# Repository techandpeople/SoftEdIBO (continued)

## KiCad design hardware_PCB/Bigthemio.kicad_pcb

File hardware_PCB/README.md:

# Hardware (PCB) files

KiCad design files for the SoftEdIBO node boards:

- **Top-level KiCad project** (the `.kicad_pro` / `.kicad_sch` / `.kicad_pcb`
  files in this directory) — the **multiplexed board** (`node_multiplexed`):
  ESP32-WROOM-32, 74HC4067 sensor mux, PCA9685-driven valves (ULN2803 drivers),
  up to 6 pumps, XGZP6847A pressure sensors.
- **Nested KiCad project** (the subdirectory with its own `.kicad_pro`) — the
  **direct board** (`node_direct`): ESP32-WROOM-32, 3 chambers on direct ADC
  sensors, ULN2803-driven valves, 2 onboard pumps.
- `Data_sheets/` — component datasheets (pump/valve drivers, XGZP6847A pressure
  sensor).
- `libraries/` — shared KiCad symbol/footprint libraries;
  `logic_I2C.kicad_sch` — shared I2C logic sheet.

> The project files carry legacy names on disk; in code and docs the boards are
> always referred to by their functional names — the **direct board**
> (`node_direct`, firmware env `direct`) and the **multiplexed board**
> (`node_multiplexed`, firmware env `multiplexed`). See
> [firmware/node_actuator/](../firmware/node_actuator/).

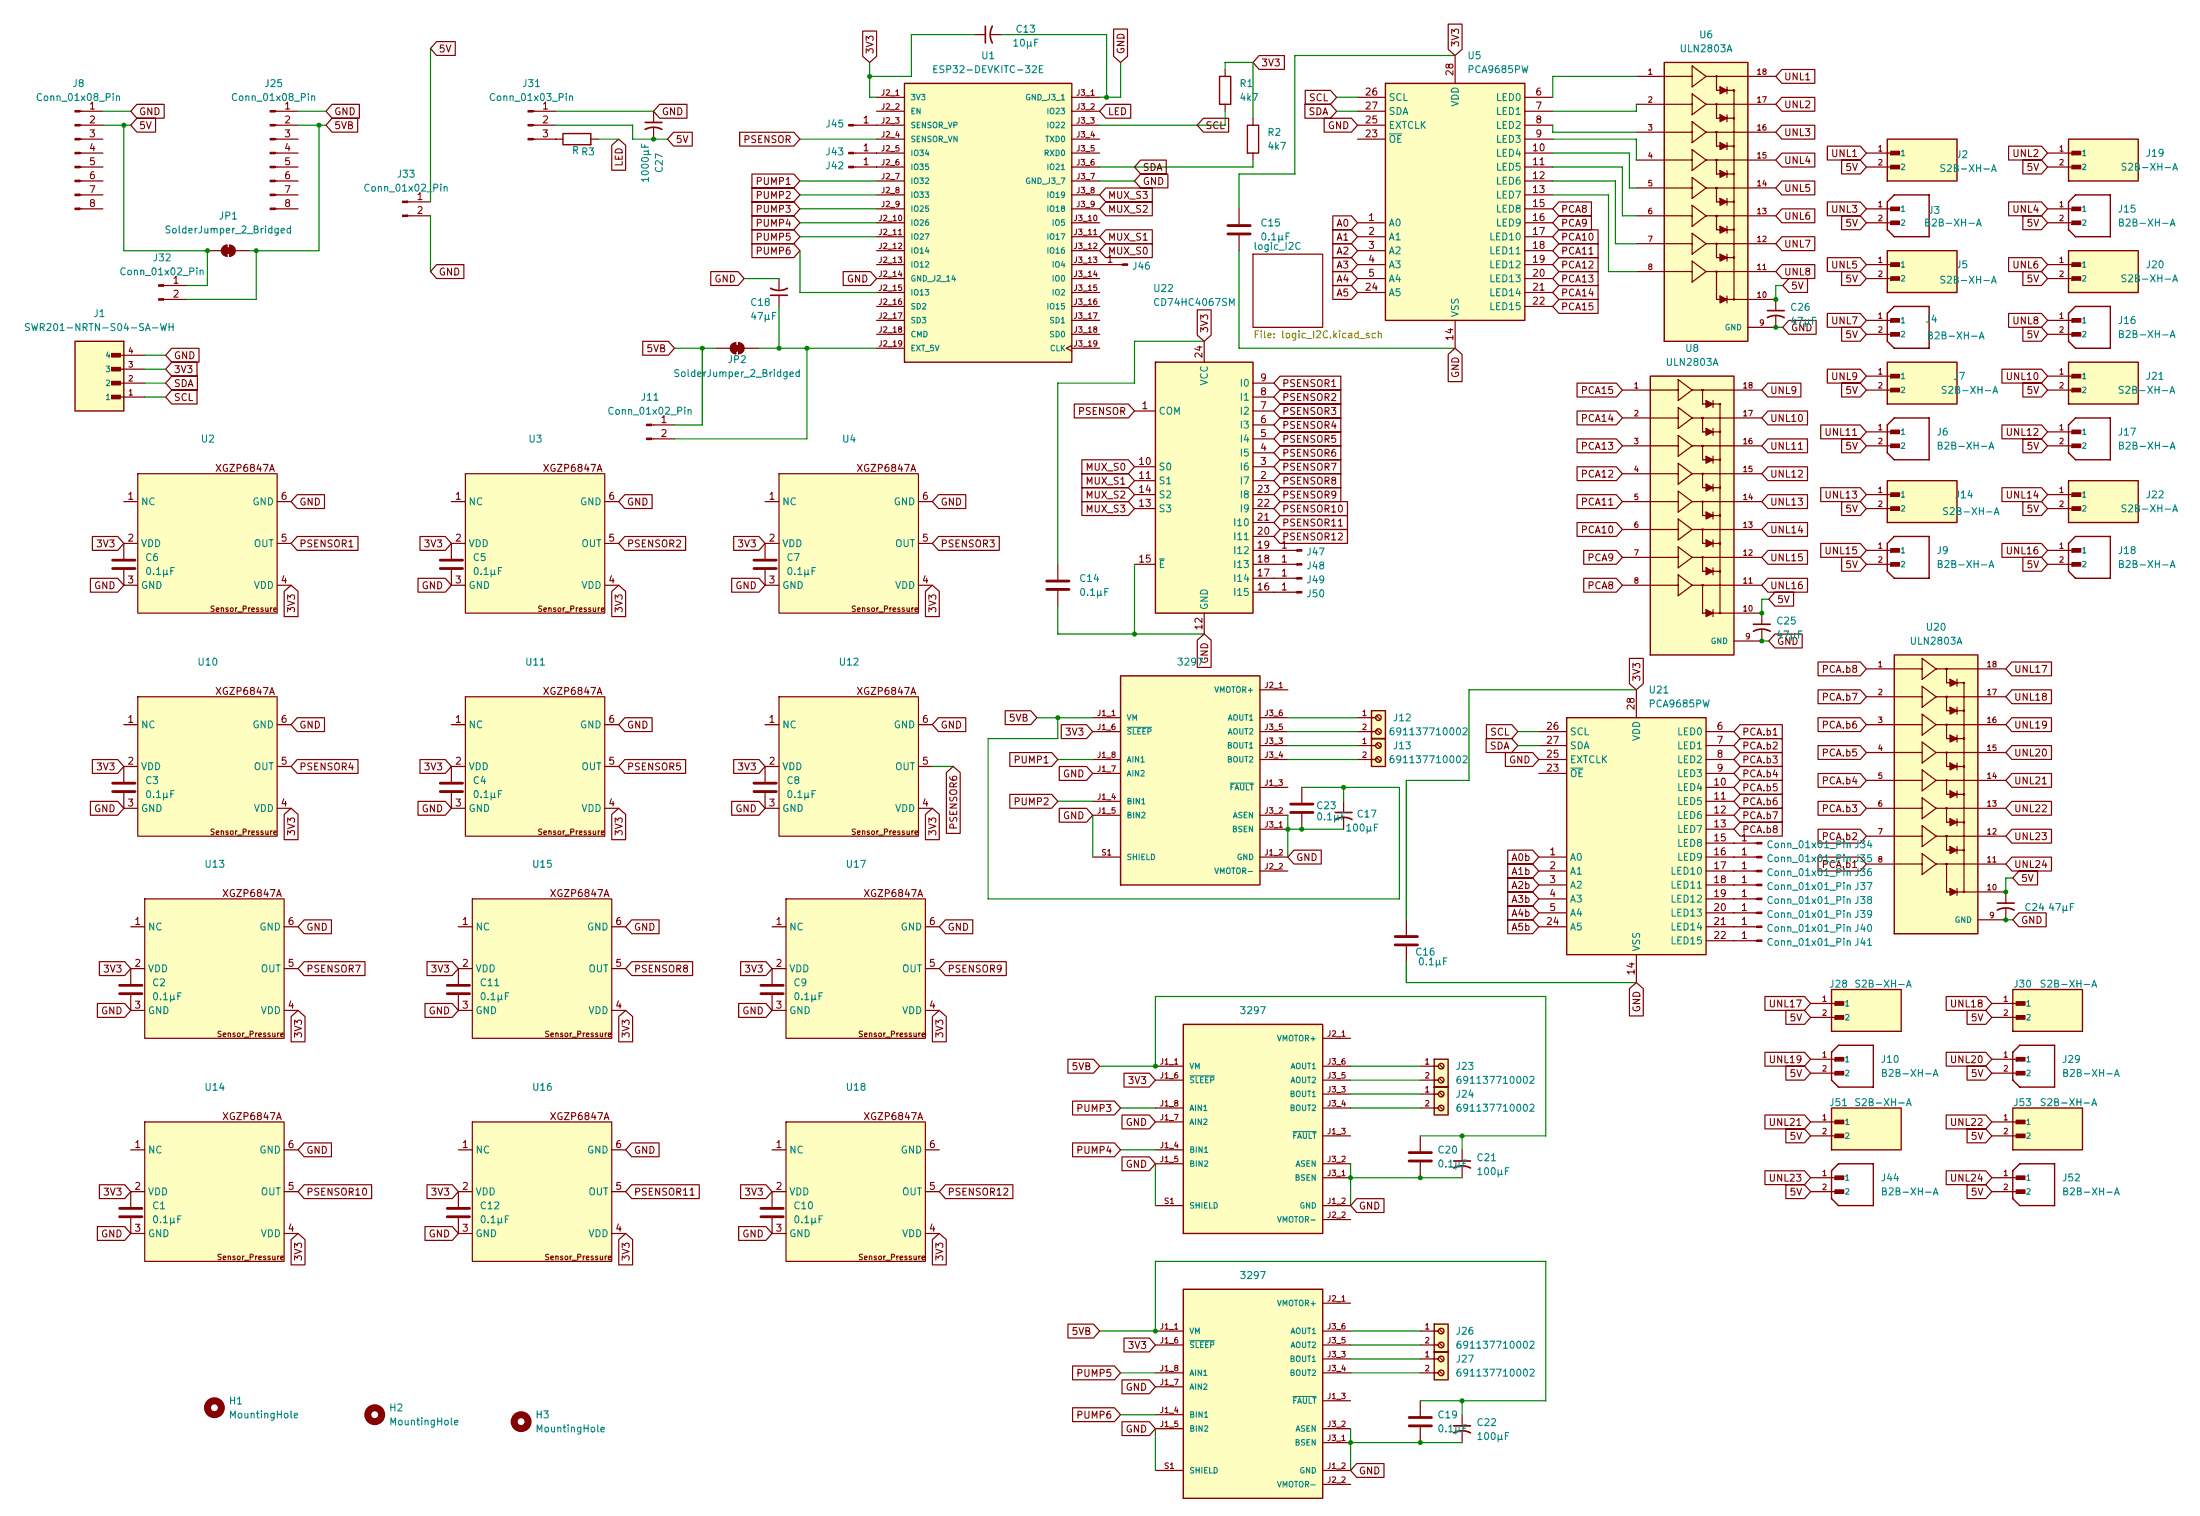
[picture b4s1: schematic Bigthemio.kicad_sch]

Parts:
C1, C2, C3, C4, C5, C6, C7, C8, C9, C10, C11, C12, C14, C15, C16, C19, C20, C23: 0.1µF; C_Disc_D5.0mm_W2.5mm_P5.00mm
C13: 10µF; CP_Radial_D5.0mm_P2.00mm
C17, C21, C22: 100µF; CP_Radial_D5.0mm_P2.00mm
C18, C24, C25, C26: 47µF; CP_Radial_D5.0mm_P2.00mm
C27: 1000µF; CP_Radial_D5.0mm_P2.00mm
H1, H2, H3: MountingHole; MountingHole_4.3mm_M4
J1: SWR201-NRTN-S04-SA-WH; SULLINS_SWR201-NRTN-S04-SA-WH; PARTREV A
J2, J5, J7, J14, J19, J20, J21, J22, J28, J30, J51, J53: S2B-XH-A; JST_S2B-XH-A
J3, J4, J6, J9, J10, J15, J16, J17, J18, J29, J44, J52: B2B-XH-A; JST_B2B-XH-A; PARTREV N/A
J8, J25: Conn_01x08_Pin; PinHeader_1x08_P2.54mm_Vertical
J11, J32, J33: Conn_01x02_Pin; PinHeader_1x02_P2.54mm_Vertical
J12, J13, J23, J24, J26, J27: 691137710002
J31: Conn_01x03_Pin; PinHeader_1x03_P2.54mm_Vertical
J34, J35, J36, J37, J38, J39, J40, J41, J42, J43, J45, J46, J47, J48, J49, J50: Conn_01x01_Pin; PinHeader_1x01_P2.54mm_Vertical
JP1, JP2: SolderJumper_2_Bridged; SolderJumper-2_P1.3mm_Bridged2Bar_RoundedPad1.0x1.5mm
R1, R2: 4k7; R_Axial_DIN0207_L6.3mm_D2.5mm_P7.62mm_Horizontal
R3: R; R_Axial_DIN0207_L6.3mm_D2.5mm_P7.62mm_Horizontal
U1: ESP32-DEVKITC-32E; MODULE_ESP32-DEVKITC-32E; PARTREV 1.4
U2, U3, U4, U10, U11, U12, U13, U14, U15, U16, U17, U18: XGP6847A_TiagoDias
U5, U21: PCA9685PW; TSSOP-28_4.4x9.7mm_P0.65mm
U6, U8, U20: ULN2803A; UNL; PARTREV 4
U7, U9, U19: 3297; MODULE_3297; PARTREV 2020-11-20
U22: CD74HC4067SM; SSOP-24_5.3x8.2mm_P0.65mm

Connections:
3V3: C1.1, C2.1, C3.1, C4.1, C5.1, C6.1, C7.1, C8.1, C9.1, C10.1, C11.1, C12.1, C13.1, C14.1, C15.1, C16.1, J1.3, R1.1, R2.1, U1.J2_1 (3V3), U2.2 (VDD), U2.4 (VDD), U3.2 (VDD), U3.4 (VDD), U4.2 (VDD), U4.4 (VDD), U5.28 (VDD), U7.J1_6 (~SLEEP), U9.J1_6 (~SLEEP), U10.2 (VDD), U10.4 (VDD), U11.2 (VDD), U11.4 (VDD), U12.2 (VDD), U12.4 (VDD), U13.2 (VDD), U13.4 (VDD), U14.2 (VDD), U14.4 (VDD), U15.2 (VDD), U15.4 (VDD), U16.2 (VDD), U16.4 (VDD), U17.2 (VDD), U17.4 (VDD), U18.2 (VDD), U18.4 (VDD), U19.J1_6 (~SLEEP), U21.28 (VDD), U22.24 (VCC); also elsewhere on the board
5V: C24.1, C25.1, C26.1, C27.2, J2.2, J3.2, J4.2, J5.2, J6.2, J7.2, J8.2, J9.2, J10.2, J14.2, J15.2, J16.2, J17.2, J18.2, J19.2, J20.2, J21.2, J22.2, J28.2, J29.2, J30.2, J31.2, J32.1, J33.1, J44.2, J51.2, J52.2, J53.2, JP1.1 (A), U6.10, U8.10, U20.10
5VB: C17.1, C19.1, C20.1, C21.1, C22.1, C23.1, J11.1, J25.2, J32.2, JP1.2 (B), JP2.1 (A), U7.J1_1 (VM), U9.J1_1 (VM), U19.J1_1 (VM)
A0: U5.1 (A0); also elsewhere on the board
A0b: U21.1 (A0); also elsewhere on the board
A1: U5.2 (A1); also elsewhere on the board
A1b: U21.2 (A1); also elsewhere on the board
A2: U5.3 (A2); also elsewhere on the board
A2b: U21.3 (A2); also elsewhere on the board
A3: U5.4 (A3); also elsewhere on the board
A3b: U21.4 (A3); also elsewhere on the board
A4: U5.5 (A4); also elsewhere on the board
A4b: U21.5 (A4); also elsewhere on the board
A5: U5.24 (A5); also elsewhere on the board
A5b: U21.24 (A5); also elsewhere on the board
GND: C1.2, C2.2, C3.2, C4.2, C5.2, C6.2, C7.2, C8.2, C9.2, C10.2, C11.2, C12.2, C13.2, C14.2, C15.2, C16.2, C17.2, C18.2, C19.2, C20.2, C21.2, C22.2, C23.2, C24.2, C25.2, C26.2, C27.1, J1.4, J8.1, J25.1, J31.1, J33.2, U1.J2_14 (GND_J2_14), U1.J3_1 (GND_J3_1), U1.J3_7 (GND_J3_7), U2.3 (GND), U2.6 (GND), U3.3 (GND), U3.6 (GND), U4.3 (GND), U4.6 (GND), U5.14 (VSS), U5.25 (EXTCLK), U6.9 (GND), U7.J1_2 (GND), U7.J1_5 (BIN2), U7.J1_7 (AIN2), U7.J3_1 (BSEN), U7.J3_2 (ASEN), U7.S1 (SHIELD), U7.S2 (SHIELD), U8.9 (GND), U9.J1_2 (GND), U9.J1_5 (BIN2), U9.J1_7 (AIN2), U9.J3_1 (BSEN), U9.J3_2 (ASEN), U9.S1 (SHIELD), U9.S2 (SHIELD), U10.3 (GND), U10.6 (GND), U11.3 (GND), U11.6 (GND), U12.3 (GND), U12.6 (GND), U13.3 (GND), U13.6 (GND), U14.3 (GND), U14.6 (GND), U15.3 (GND), U15.6 (GND), U16.3 (GND), U16.6 (GND), U17.3 (GND), U17.6 (GND), U18.3 (GND), U19.J1_2 (GND), U19.J1_5 (BIN2), U19.J1_7 (AIN2), U19.J3_1 (BSEN), U19.J3_2 (ASEN), U19.S1 (SHIELD), U19.S2 (SHIELD), U20.9 (GND), U21.14 (VSS), U21.25 (EXTCLK), U22.12 (GND), U22.15 (~E); also elsewhere on the board
LED: R3.2, U1.J3_2 (IO23)
MUX_S0: U1.J3_12 (IO16), U22.10 (S0)
MUX_S1: U1.J3_11 (IO17), U22.11 (S1)
MUX_S2: U1.J3_9 (IO18), U22.14 (S2)
MUX_S3: U1.J3_8 (IO19), U22.13 (S3)
unnamed: C18.1, J11.2, JP2.2 (B), U1.J2_19 (EXT_5V)
unnamed: J31.3, R3.1
unnamed: J34.1, U21.15 (LED8)
unnamed: J35.1, U21.16 (LED9)
unnamed: J36.1, U21.17 (LED10)
unnamed: J37.1, U21.18 (LED11)
unnamed: J38.1, U21.19 (LED12)
unnamed: J39.1, U21.20 (LED13)
unnamed: J40.1, U21.21 (LED14)
unnamed: J41.1, U21.22 (LED15)
unnamed: J42.1, U1.J2_6 (IO35)
unnamed: J43.1, U1.J2_5 (IO34)
unnamed: J45.1, U1.J2_3 (SENSOR_VP)
unnamed: J46.1, U1.J3_13 (IO4)
unnamed: J47.1, U22.19 (I12)
unnamed: J48.1, U22.18 (I13)
unnamed: J49.1, U22.17 (I14)
unnamed: J50.1, U22.16 (I15)
unnamed: U5.6 (LED0), U6.1
unnamed: U5.7 (LED1), U6.2
unnamed: U5.8 (LED2), U6.3
unnamed: U5.9 (LED3), U6.4
unnamed: U5.10 (LED4), U6.5
unnamed: U5.11 (LED5), U6.6
unnamed: U5.12 (LED6), U6.7
unnamed: U5.13 (LED7), U6.8
unnamed: J12.1, U7.J3_6 (AOUT1)
unnamed: J12.2, U7.J3_5 (AOUT2)
unnamed: J13.1, U7.J3_3 (BOUT1)
unnamed: J13.2, U7.J3_4 (BOUT2)
unnamed: J23.1, U9.J3_6 (AOUT1)
unnamed: J23.2, U9.J3_5 (AOUT2)
unnamed: J24.1, U9.J3_3 (BOUT1)
unnamed: J24.2, U9.J3_4 (BOUT2)
unnamed: J26.1, U19.J3_6 (AOUT1)
unnamed: J26.2, U19.J3_5 (AOUT2)
unnamed: J27.1, U19.J3_3 (BOUT1)
unnamed: J27.2, U19.J3_4 (BOUT2)
PCA8: U5.15 (LED8), U8.8
PCA9: U5.16 (LED9), U8.7
PCA10: U5.17 (LED10), U8.6
PCA11: U5.18 (LED11), U8.5
PCA12: U5.19 (LED12), U8.4
PCA13: U5.20 (LED13), U8.3
PCA14: U5.21 (LED14), U8.2
PCA15: U5.22 (LED15), U8.1
PCA.b1: U20.8, U21.6 (LED0)
PCA.b2: U20.7, U21.7 (LED1)
PCA.b3: U20.6, U21.8 (LED2)
PCA.b4: U20.5, U21.9 (LED3)
PCA.b5: U20.4, U21.10 (LED4)
PCA.b6: U20.3, U21.11 (LED5)
PCA.b7: U20.2, U21.12 (LED6)
PCA.b8: U20.1, U21.13 (LED7)
PSENSOR: U1.J2_4 (SENSOR_VN), U22.1 (COM)
PSENSOR1: U2.5 (OUT), U22.9 (I0)
PSENSOR2: U3.5 (OUT), U22.8 (I1)
PSENSOR3: U4.5 (OUT), U22.7 (I2)
PSENSOR4: U10.5 (OUT), U22.6 (I3)
PSENSOR5: U11.5 (OUT), U22.5 (I4)
PSENSOR6: U12.5 (OUT), U22.4 (I5)
PSENSOR7: U13.5 (OUT), U22.3 (I6)
PSENSOR8: U15.5 (OUT), U22.2 (I7)
PSENSOR9: U17.5 (OUT), U22.23 (I8)
PSENSOR10: U14.5 (OUT), U22.22 (I9)
PSENSOR11: U16.5 (OUT), U22.21 (I10)
PSENSOR12: U18.5 (OUT), U22.20 (I11)
PUMP1: U1.J2_7 (IO32), U7.J1_8 (AIN1)
PUMP2: U1.J2_8 (IO33), U7.J1_4 (BIN1)
PUMP3: U1.J2_9 (IO25), U9.J1_8 (AIN1)
PUMP4: U1.J2_10 (IO26), U9.J1_4 (BIN1)
PUMP5: U1.J2_11 (IO27), U19.J1_8 (AIN1)
PUMP6: U1.J2_15 (IO13), U19.J1_4 (BIN1)
SCL: J1.1, R1.2, U1.J3_3 (IO22), U5.26 (SCL), U21.26 (SCL)
SDA: J1.2, R2.2, U1.J3_6 (IO21), U5.27 (SDA), U21.27 (SDA)
UNL1: J2.1, U6.18
UNL2: J19.1, U6.17
UNL3: J3.1, U6.16
UNL4: J15.1, U6.15
UNL5: J5.1, U6.14
UNL6: J20.1, U6.13
UNL7: J4.1, U6.12
UNL8: J16.1, U6.11
UNL9: J7.1, U8.18
UNL10: J21.1, U8.17
UNL11: J6.1, U8.16
UNL12: J17.1, U8.15
UNL13: J14.1, U8.14
UNL14: J22.1, U8.13
UNL15: J9.1, U8.12
UNL16: J18.1, U8.11
UNL17: J28.1, U20.18
UNL18: J30.1, U20.17
UNL19: J10.1, U20.16
UNL20: J29.1, U20.15
UNL21: J51.1, U20.14
UNL22: J53.1, U20.13
UNL23: J44.1, U20.12
UNL24: J52.1, U20.11

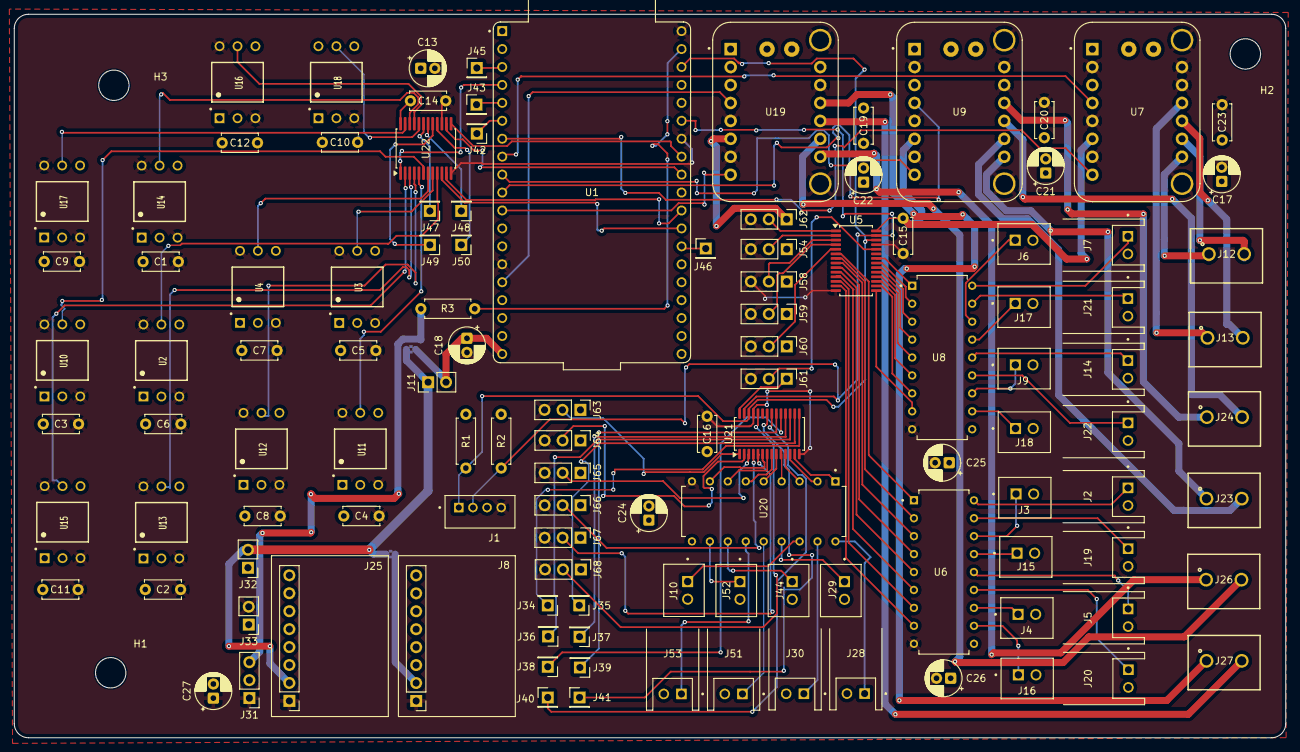
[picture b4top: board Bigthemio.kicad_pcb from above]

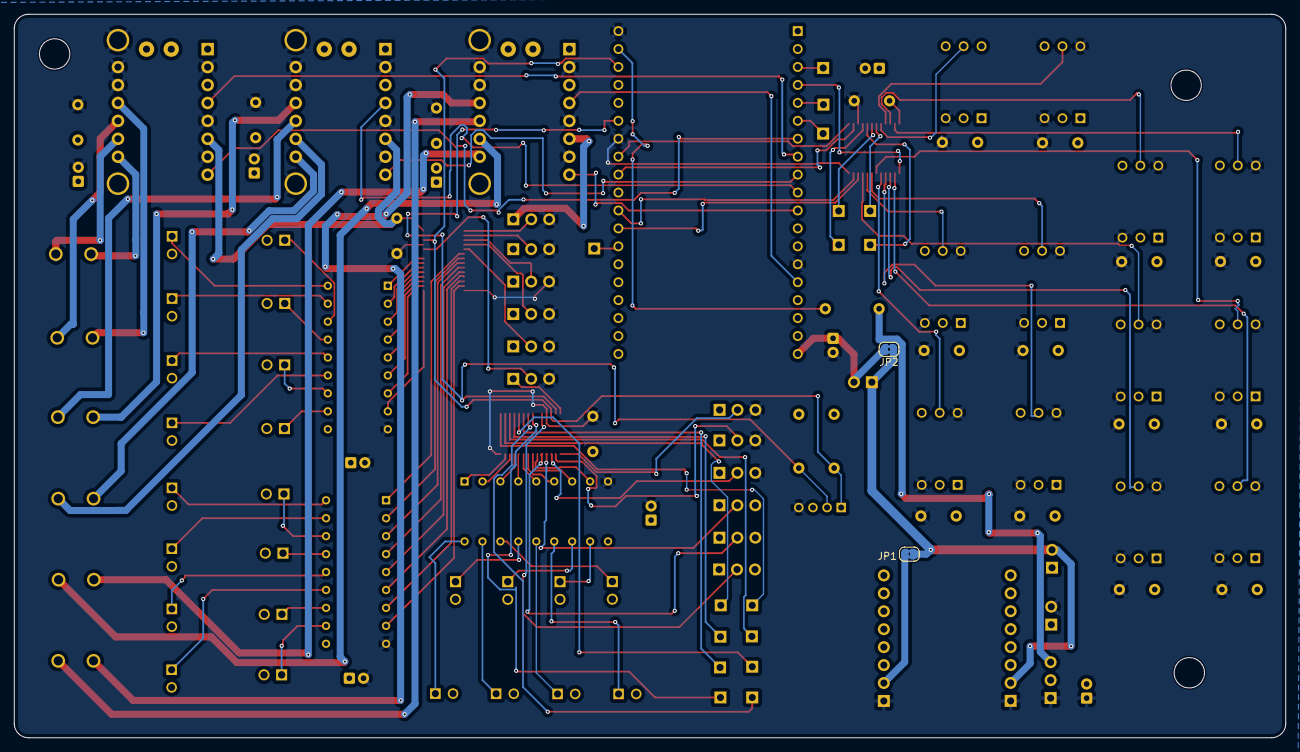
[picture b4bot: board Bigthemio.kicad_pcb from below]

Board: 4 copper layers, 180.1 x 102.5 mm, 122 parts (2 on the bottom side), 120 nets.

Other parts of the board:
J54, J58, J59, J60, J61, J62, J63, J64, J65, J66, J67, J68: Conn_01x03_Pin; PinHeader_1x03_P2.54mm_Vertical

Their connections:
3V3: J54.1, J58.1, J59.1, J60.1, J61.1, J62.1, J63.1, J64.1, J65.1, J66.1, J67.1, J68.1; also elsewhere on the board
A0: J62.2; also elsewhere on the board
A0b: J63.2; also elsewhere on the board
A1: J54.2; also elsewhere on the board
A1b: J64.2; also elsewhere on the board
A2: J58.2; also elsewhere on the board
A2b: J65.2; also elsewhere on the board
A3: J59.2; also elsewhere on the board
A3b: J66.2; also elsewhere on the board
A4: J60.2; also elsewhere on the board
A4b: J67.2; also elsewhere on the board
A5: J61.2; also elsewhere on the board
A5b: J68.2; also elsewhere on the board
GND: J54.3, J58.3, J59.3, J60.3, J61.3, J62.3, J63.3, J64.3, J65.3, J66.3, J67.3, J68.3; also elsewhere on the board

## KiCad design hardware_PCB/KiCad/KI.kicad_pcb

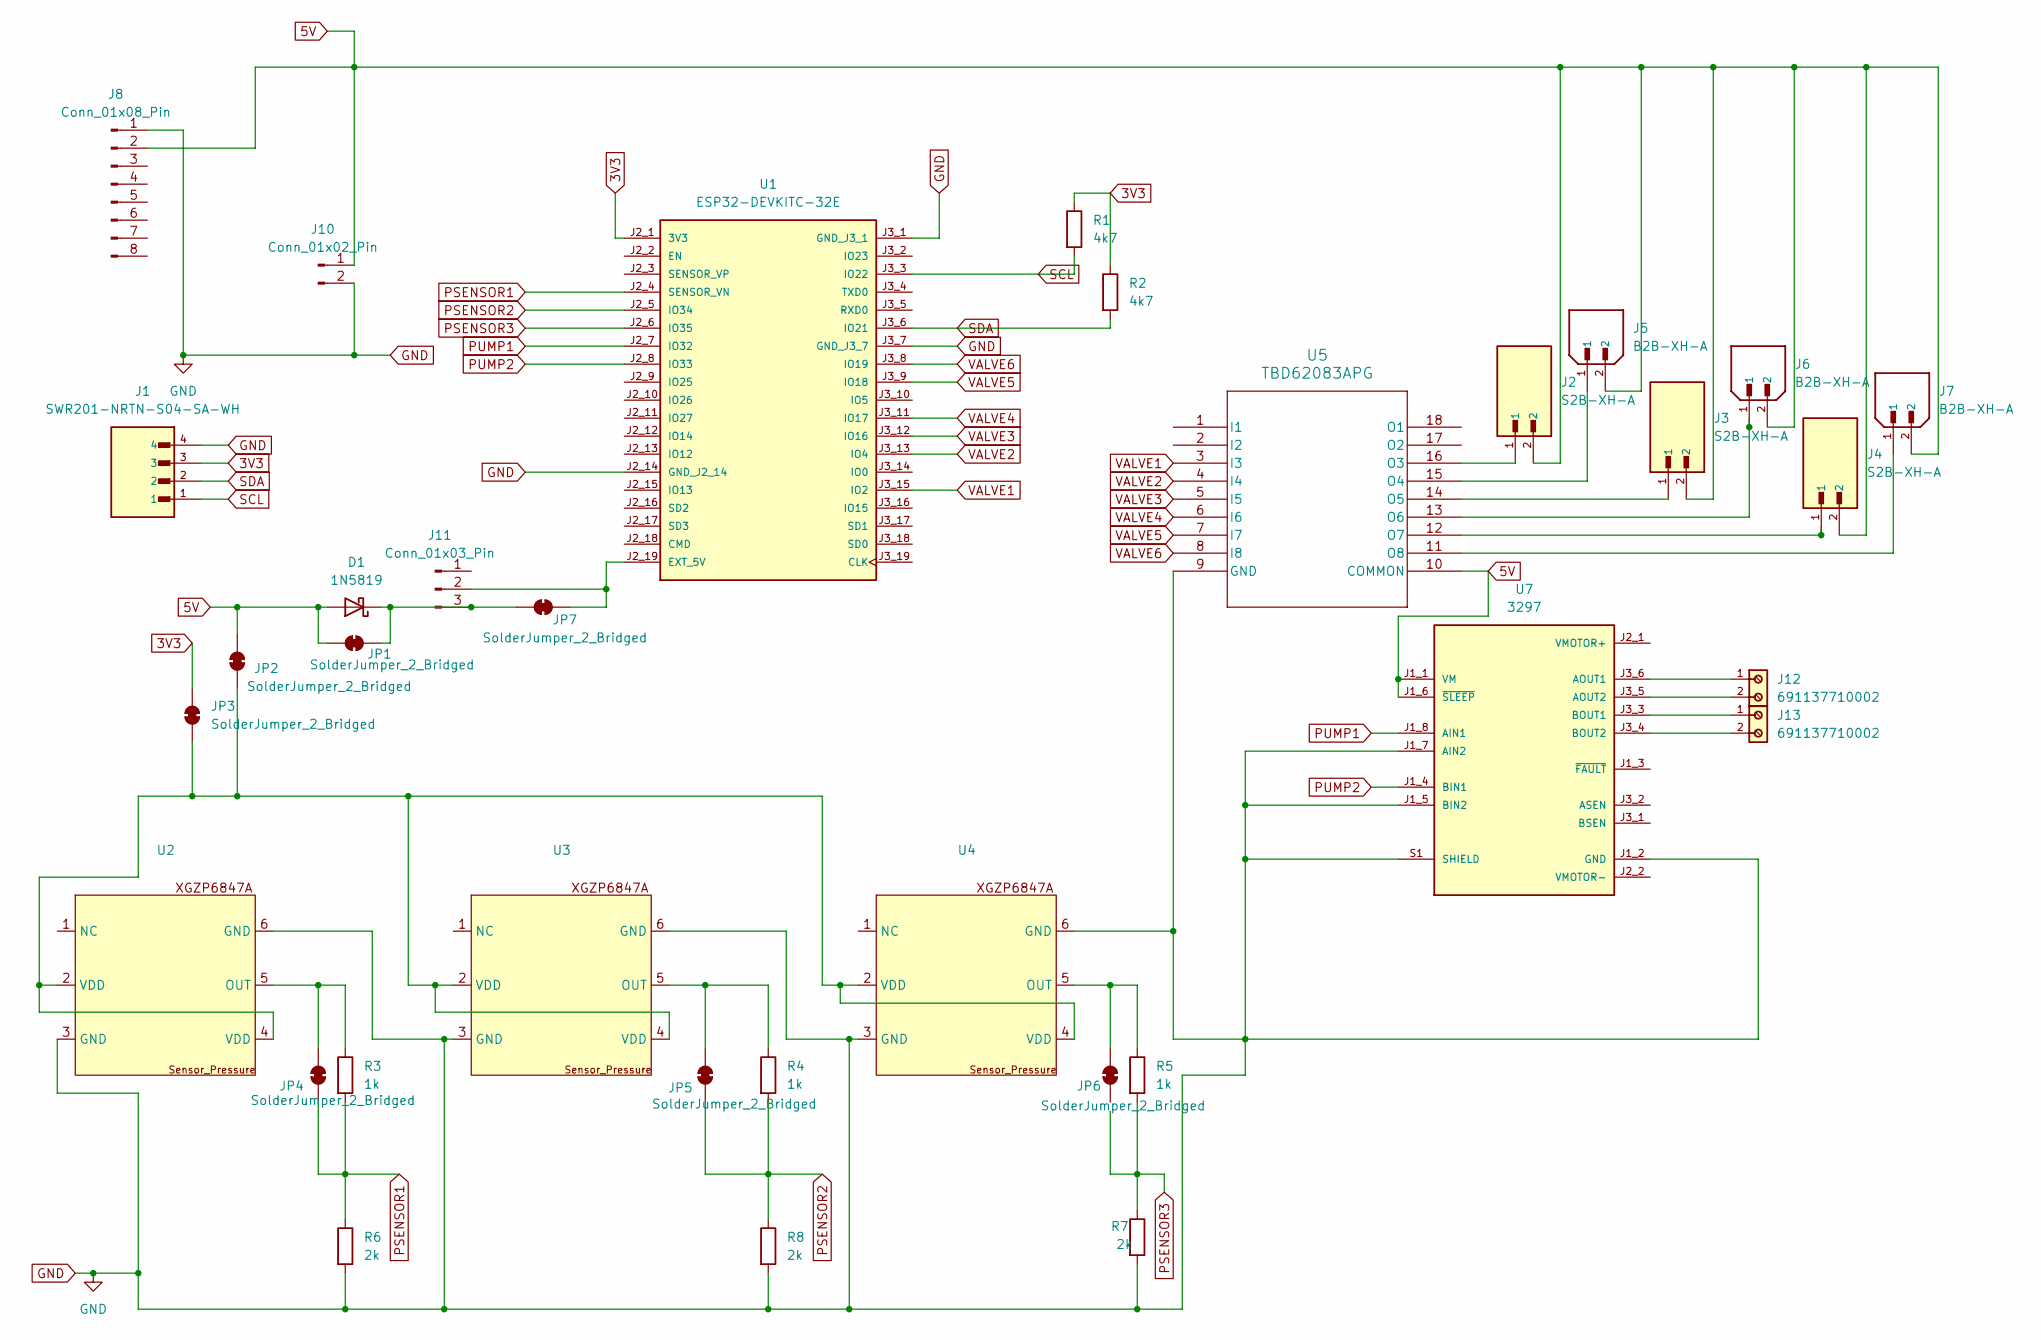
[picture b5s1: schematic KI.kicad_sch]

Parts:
D1: 1N5819; D_DO-41_SOD81_P10.16mm_Horizontal
J1: SWR201-NRTN-S04-SA-WH; SULLINS_SWR201-NRTN-S04-SA-WH; PARTREV A
J2, J3, J4: S2B-XH-A; JST_S2B-XH-A
J5, J6, J7: B2B-XH-A; JST_B2B-XH-A; PARTREV N/A
J8: Conn_01x08_Pin; PinHeader_1x08_P2.54mm_Vertical
J10: Conn_01x02_Pin; PinHeader_1x02_P2.54mm_Vertical
J11: Conn_01x03_Pin; PinHeader_1x03_P2.54mm_Vertical
J12, J13: 691137710002
JP1, JP2, JP3, JP4, JP5, JP6, JP7: SolderJumper_2_Bridged; SolderJumper-2_P1.3mm_Bridged_RoundedPad1.0x1.5mm
R1, R2: 4k7; R_Axial_DIN0207_L6.3mm_D2.5mm_P7.62mm_Horizontal
R3, R4, R5: 1k; R_Axial_DIN0207_L6.3mm_D2.5mm_P7.62mm_Horizontal
R6, R7, R8: 2k; R_Axial_DIN0207_L6.3mm_D2.5mm_P7.62mm_Horizontal
U1: ESP32-DEVKITC-32E; MODULE_ESP32-DEVKITC-32E; PARTREV 1.4
U2, U3, U4: XGP6847A
U5: TBD62083APG
U7: 3297; MODULE_3297; PARTREV 2020-11-20

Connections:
3V3: J1.3, JP3.2 (B), R1.1, R2.1, U1.J2_1 (3V3)
5V: D1.2 (A), J2.2, J3.2, J4.2, J5.2, J6.2, J7.2, J8.2, J10.1, JP1.1 (A), JP2.2 (B), U5.10 (COMMON), U7.J1_1 (VM), U7.J1_6 (~SLEEP)
GND: J1.4, J8.1, J10.2, R6.2, R7.2, R8.2, U1.J2_14 (GND_J2_14), U1.J3_1 (GND_J3_1), U1.J3_7 (GND_J3_7), U2.3 (GND), U2.6 (GND), U3.3 (GND), U3.6 (GND), U4.3 (GND), U4.6 (GND), U5.9 (GND), U7.J1_2 (GND), U7.J1_5 (BIN2), U7.J1_7 (AIN2), U7.S1 (SHIELD), U7.S2 (SHIELD)
unnamed: D1.1 (K), J11.3, JP1.2 (B), JP7.1 (A)
unnamed: J11.2, JP7.2 (B), U1.J2_19 (EXT_5V)
unnamed: JP2.1 (A), JP3.1 (A), U2.2 (VDD), U2.4 (VDD), U3.2 (VDD), U3.4 (VDD), U4.2 (VDD), U4.4 (VDD)
unnamed: JP4.2 (B), R3.1, U2.5 (OUT)
unnamed: JP5.2 (B), R4.1, U3.5 (OUT)
unnamed: JP6.2 (B), R5.1, U4.5 (OUT)
unnamed: J2.1, U5.16 (O3)
unnamed: J5.1, U5.15 (O4)
unnamed: J3.1, U5.14 (O5)
unnamed: J6.1, U5.13 (O6)
unnamed: J4.1, U5.12 (O7)
unnamed: J7.1, U5.11 (O8)
unnamed: J12.1, U7.J3_6 (AOUT1)
unnamed: J12.2, U7.J3_5 (AOUT2)
unnamed: J13.1, U7.J3_3 (BOUT1)
unnamed: J13.2, U7.J3_4 (BOUT2)
PSENSOR1: JP4.1 (A), R3.2, R6.1, U1.J2_4 (SENSOR_VN)
PSENSOR2: JP5.1 (A), R4.2, R8.1, U1.J2_5 (IO34)
PSENSOR3: R5.2, R7.1, U1.J2_6 (IO35)
PUMP1: U1.J2_7 (IO32), U7.J1_8 (AIN1)
PUMP2: U1.J2_8 (IO33), U7.J1_4 (BIN1)
SCL: J1.1, R1.2, U1.J3_3 (IO22)
SDA: J1.2, R2.2, U1.J3_6 (IO21)
VALVE1: U1.J3_15 (IO2), U5.3 (I3)
VALVE2: U1.J3_13 (IO4), U5.4 (I4)
VALVE3: U1.J3_12 (IO16), U5.5 (I5)
VALVE4: U1.J3_11 (IO17), U5.6 (I6)
VALVE5: U1.J3_9 (IO18), U5.7 (I7)
VALVE6: U1.J3_8 (IO19), U5.8 (I8)

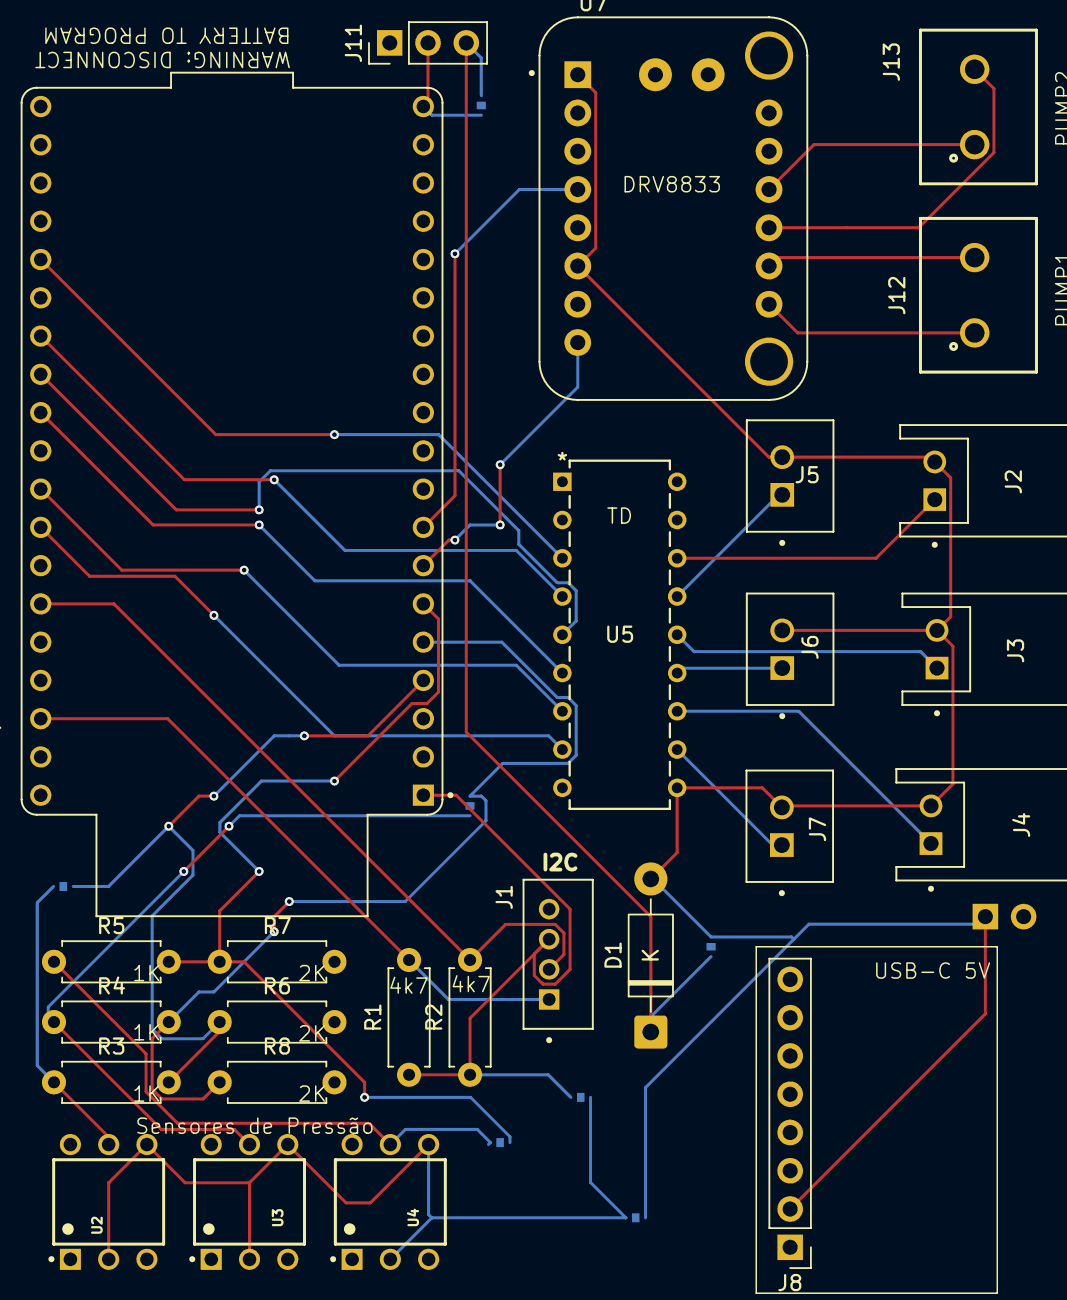
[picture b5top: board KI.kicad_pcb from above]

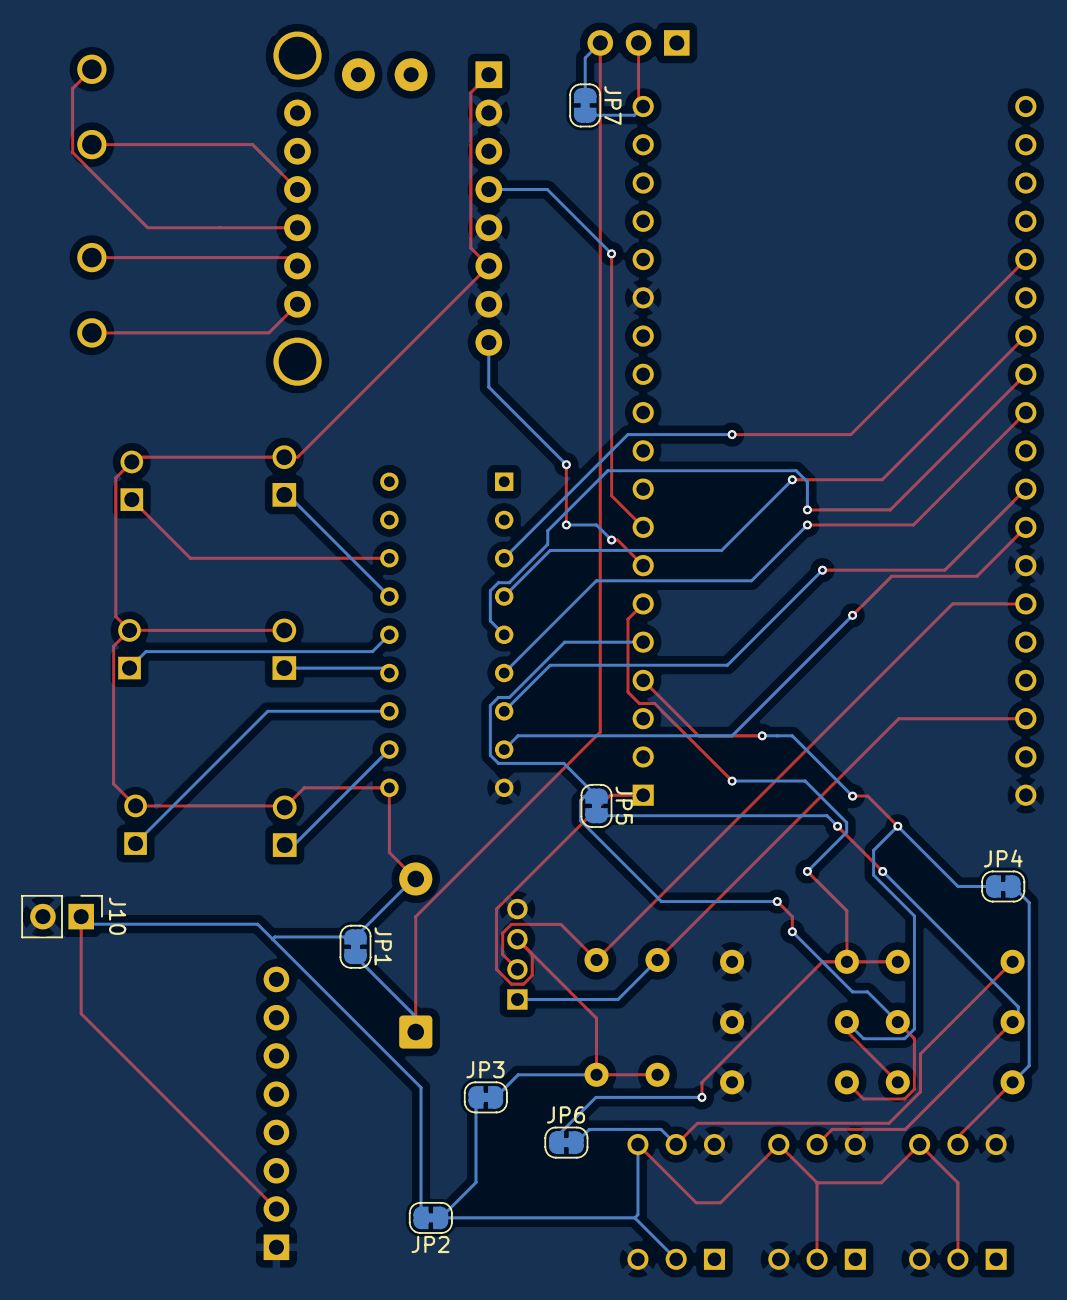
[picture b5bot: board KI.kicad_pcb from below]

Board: 2 copper layers, 34 parts (8 on the bottom side), 32 nets.

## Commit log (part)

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2026-03-02 Added temporary icon
2026-03-02 Fix unacepted MacOS file name in Windows - Rename '3297 EDA - Download de model.textClipping'
2026-03-02 Fix updater new version download
2026-03-04 Started firmware develop
2026-03-04 Fixed firmware
2026-03-04 firmware in build
2026-03-04 Now only valid USB devices are show in robot panel
2026-03-04 *.bin are built with CI
2026-03-04 Fix updater.py - Comparing build dates correctly now
2026-03-04 Hability to call install.sh with curl | bash
2026-03-04 Fixed BASH_SOURCE[0] error
2026-03-04 Separate serial ports logic into serial_ports.py module
2026-03-04 Fixed installation permissions and icon
2026-03-04 Replaced → with =>
2026-03-06 Week changes
2026-03-07 Fix with flow_layout.py
2026-03-07 Fix installer.py
2026-03-07 Fix when user already have settings.yaml
2026-03-07 Fix permissions for new file by updater.py
2026-03-22 2026/03/22 weekend changes and fixes
2026-03-22 Fix indentation for _RAMP_TARGET_STEP in SimulatedController
2026-03-25 Fixed SetupWizard Flashing progress bar
2026-03-25 Add max pressure configuration for air chambers and enhance logging setup
    - Updated .gitignore to exclude log files.
    - Enhanced README.md with details on per-chamber max pressure settings.
    - Modified air chamber firmware to enforce max pressure limits.
    - Implemented max pressure settings in simulated and real robot controllers.
    - Added centralized logging configuration to improve debugging and error tracking.
2026-03-25 Enhance updater logging and fix esptool command syntax in setup wizard
2026-03-25 Update README and firmware to reflect changes in air chamber node configuration and pump control
2026-03-25 Enhance status reporting by adding raw ADC values and percentage calculation for each chamber
2026-03-31 Gateway and Debug
2026-03-31 Refactor logging configuration to support per-user log directories across platforms
2026-03-31 Fix updater, crash handler
2026-03-31 kPa instead of % for chamber max pressures
2026-03-31 Several Fixes
2026-03-31 updater log
2026-03-31 debugging updater...
2026-04-01 New system with air reservoirs
2026-04-01 build fix
2026-04-02 Bug fix
2026-04-28 New system according to the new PCBs
2026-05-01 Tanks in the monitor
2026-05-01 Add Themio PCB file
2026-05-01 Add files via upload
    Just open the '.kicad_pro'
2026-05-02 Add files via upload
    Add the capasitors values
2026-05-12 hw(afe): lock 5V/2.5V receiver frontend, fix bias sag & adc clamp
    - OPA2356 shifted to 5V rail for dynamic headroom
    - 2.5V virtual ground with 10k/10k divider
    - Stage 2 gain tuned to 2.2 (1.2k/1k) to prevent saturation
    - Implement Option B BAT54S DC restoration (baseline 2.4V)
    - Orient BZT52C3V3 Zener for 3.3V MCU protection
    - Verify 13.56MHz transient response and 341-step ADC window via NGSpice
2026-05-12 hw(afe): lock 5V/2.5V receiver frontend
    - Fixed bias sag with 1.2k/1k feedback network
    - Implemented DC restoration floor at 2.4V
    - Confirmed 3.3V Zener protection on PA1
    - Verified 13.56MHz transient response via NGSpice
2026-05-12 ngspice simulation say initial design would be to voltage amplification would be miniam high cross talk correcting with TIA higher voltage and zener for interface with MCU since cant take the higher 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
2026-05-13 finished preliminary drawing
2026-05-15 Initial commit: Nesting project files under capacitance subdirectory
2026-05-15 reoganizing
2026-05-16 with douple spi connection
2026-05-17 reservoir_node -> multiplexed_node
2026-05-18 version wiouth diodes to maximize capacitance re thinking envolope, simulation teste on openems available and configured
2026-05-21 3D models
2026-05-21 STLs and F3d
2026-05-23 some minor improvements and firmware protocol
2026-05-26 Thymio Organ Skin Mold
2026-05-30 starting to adopt touch sensing
2026-06-01 Implementing Sensors from Yaya
2026-06-02 New firmware, ESP32 C6
2026-06-02 fix windows CI
2026-06-02 NEOpixel LED support
2026-06-02 Swapped pins inflate deflate
2026-06-03 ESP32 Nodes OTA updates support
2026-06-03 updated tests
2026-06-08 Sensors barelly working
2026-06-08 ci & ota_update fix
2026-06-17 Modular Design
2026-06-19 ML for touch patterns
2026-06-20 Time based chamber filling
2026-06-21 editable *.ui
2026-06-21 fix readme repo refs
2026-06-21 touch adptative baseline
2026-06-22 firmware: symmetric deflate time cap
2026-06-22 add touch-chamber coupling analyzer
2026-06-22 extract skin config domain logic to core
2026-06-22 monitor: chamber/tank/touch-tuning panels as .ui
2026-06-22 docs: touch coupling, pressure safety, gui arch
2026-06-22 More New 3D Models
2026-06-23 Organ GUI
2026-06-23 Adapter for 20mm Skin - Thymio
2026-06-24 Fixed simulation organ gui
2026-06-24 OTA updates maybe working now, Magnetic sensors merged with node_direct, Gateway as AP too
2026-06-24 emergency flash GUI, OTA fixed
2026-06-24 Behaviour visual editor
2026-06-26 3D models 26-06-2026
2026-06-27 friday changes
2026-06-27 27-06 morning changes
2026-06-27 fixed, chamber not deflating
2026-06-27 Saturday 27-06 work
2026-06-27 late saturday 27-06 fixes
2026-06-28 Trying to fix more thans one chambers inflating at the same time
2026-06-28 fixed multi chamber at the same time
2026-06-29 Almost working for "Piloto"
2026-06-29 Ready for "Piloto"
2026-06-29 Working for "Piloto"
2026-06-29 fix CI
2026-06-30 Multi chamber inflate/deflate working again!!
2026-06-30 prev commit docs
